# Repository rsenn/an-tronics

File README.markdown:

40106-4069-Synth \n\n 
555-Oscillator \n\n 
5V-to-12V-Converter \n\n 
Amazing-All-Band-Receiver \n\n 
Amplifier-ClassAB \n\n 
Aurel-super-regen-receiver-ASR2 \n\n 
FM-Radio-Circuit \n\n 
FM-Radio-Simple-Receiver \n\n 
FM-Simple-Regen \n\n 
Headphone-Amplifier-ClassAB-13x7 \n\n 
Headphone-Amplifier-ClassAB-alt3 \n\n 
Headphone-Amplifier-ClassAB-alt4 \n\n 
Headphone-Amplifier-ClassAB-alt \n\n 
Headphone-Amplifier-ClassAB \n\n 
MotorControllerOpto-BA6229 \n\n 
Simple-Analog-Amp-BC547 \n\n 
Simple-Charger-LiIon-OpampBased-LM324-prev \n\n 
Super-Regenerative-FM.old \n\n 
Super-Regenerative-VHF-2Transistor-RickAndersen-October2006-alt \n\n 
Super-Regenerative-VHF-KosmosX3000 \n\n 
Triangulator-LM324 \n\n 
VCF-LM324-Stereo+LFO-CableConn \n\n 
Simple-NPN-Regen-Receiver \n\n

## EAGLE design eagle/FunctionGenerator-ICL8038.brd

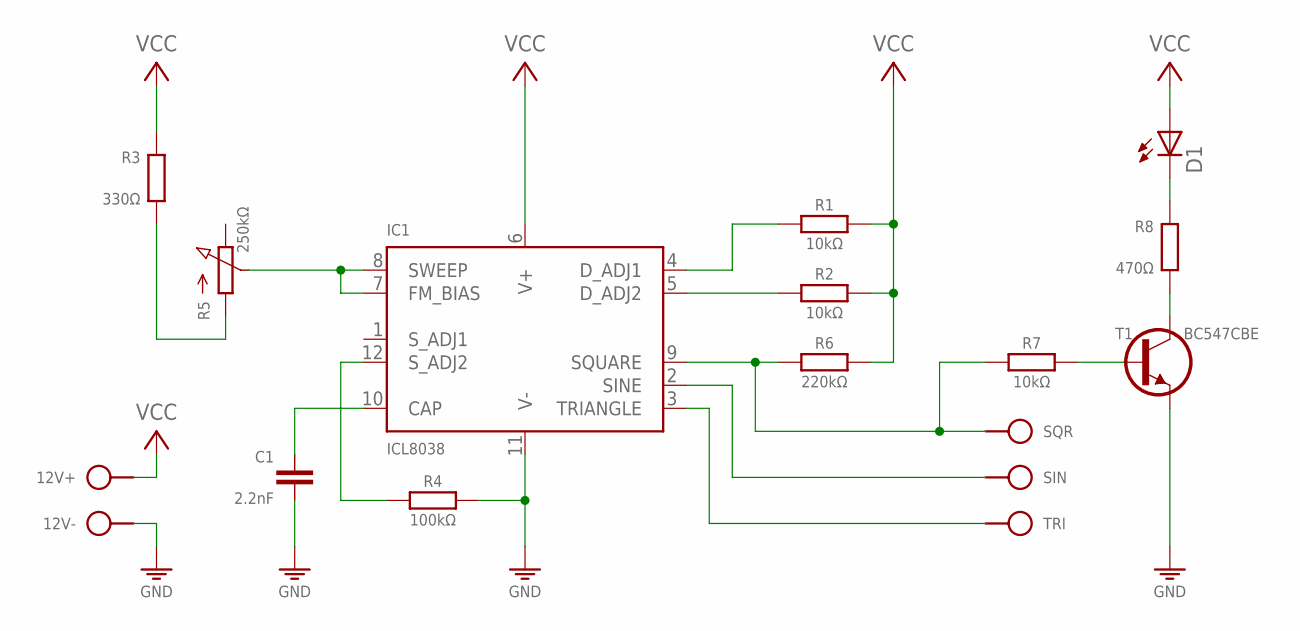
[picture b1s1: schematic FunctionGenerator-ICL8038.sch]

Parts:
12V: SPAD+-; SPAD-2
C1: 2.2nF; C050-020X044
D1: LED3MM
IC1: ICL8038; DIL14
R1, R2: 10kΩ; 0202/5
R3: 330Ω; 0202/5-V
R4: 100kΩ; 0202/5
R5: 250kΩ; POT
R6: 220kΩ; 0202/5-V
R7: 10kΩ; 0202/5-V
R8: 470Ω; 0202/5-V
SIN: SPAD
SQR: SPAD
T1: BC547CBE; TO92-CBE
TRI: SPAD

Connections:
GND: 12V.1, C1.2, IC1.11 (V-), R4.2, T1.E
unnamed: R3.1, R5.1 (A)
unnamed: IC1.4 (D_ADJ1), R1.1
unnamed: IC1.5 (D_ADJ2), R2.1
unnamed: IC1.9 (SQUARE), R6.1, R7.1, SQR.1
unnamed: IC1.12 (S_ADJ2), R4.1
unnamed: C1.1, IC1.10 (CAP)
unnamed: IC1.3 (TRIANGLE), TRI.1
unnamed: IC1.2 (SINE), SIN.1
unnamed: R7.2, T1.B
unnamed: D1.K (C), R8.2
unnamed: R8.1, T1.C
unnamed: IC1.7 (FM_BIAS), IC1.8 (SWEEP), R5.2 (S)
VCC: 12V.2, D1.A, IC1.6 (V+), R1.2, R2.2, R3.2, R6.2

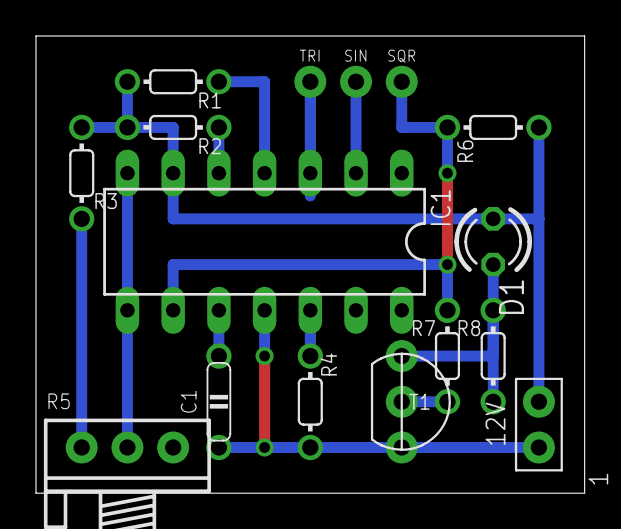
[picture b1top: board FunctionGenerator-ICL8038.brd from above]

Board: 2 copper layers, 30.5 x 25.4 mm, 16 parts (0 on the bottom side), 14 nets.

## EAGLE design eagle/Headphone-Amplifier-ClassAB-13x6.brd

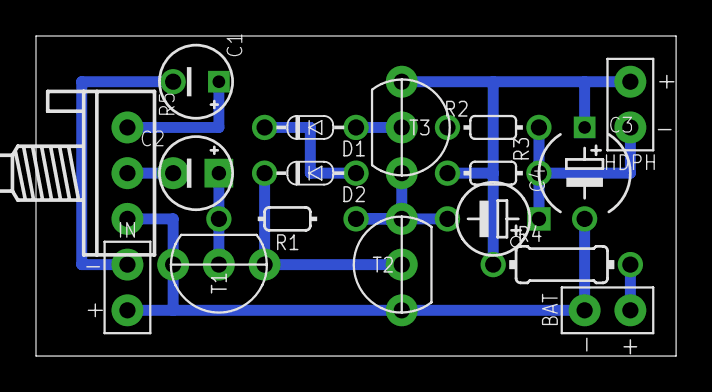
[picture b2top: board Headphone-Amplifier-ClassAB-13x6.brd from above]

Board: 2 copper layers, 35.6 x 17.8 mm, 17 parts (0 on the bottom side), 12 nets.

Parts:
BAT: SPAD+-+-; SPAD+-
C1: 4.7μF; E2.5-4/V
C2: 4.7μF; E2,5-4
C3: 100-1000μF; E5-5/V
C4: 220μF; E5-4
D1, D2: 1N4148; DO34-5
HDPH: SPAD+-+-; SPAD+-
IN: SPAD+-+-; SPAD+-
R1: 100kΩ; 0202/7
R2: 330Ω; 0202/5
R3: 100Ω; 0202/5-V
R4: 22Ω; 0204/7
R5: 100kΩ; POT
T1, T3: BC547; TO92-CBE
T2: BC557; TO92-CBE

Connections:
GND: BAT.1, C3.-, IN.2, R5.3, T1.E, T2.C
unnamed: D1.A, R2.1, T3.B
unnamed: D2.C, T1.C, T2.B
unnamed: D1.C, D2.A
unnamed: C4.-, R1.2, T2.E, T3.E
unnamed: C1.+, R5.1
unnamed: C2.-, R5.2
unnamed: C2.+, R1.1, T1.B
unnamed: C3.+, HDPH.2, R3.2, R4.1, T3.C
unnamed: C4.+, HDPH.1, R2.2, R3.1
unnamed: C1.-, IN.1
V+: BAT.2, R4.2

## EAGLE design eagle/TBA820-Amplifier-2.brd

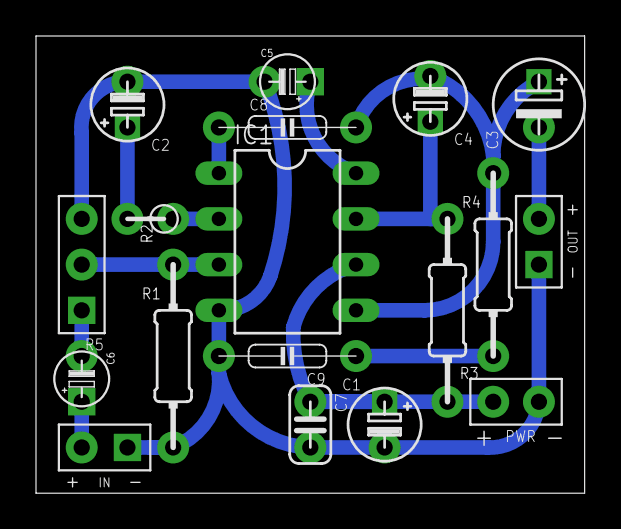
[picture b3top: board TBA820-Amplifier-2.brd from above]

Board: 2 copper layers, 30.5 x 25.4 mm, 18 parts (0 on the bottom side), 13 nets.

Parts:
C1, C2, C4: 100μF; E2.5-4/V
C3: 220μF; E2,5-5
C5: 47μF; E2,5-3
C6: 10μF; E2,5-3
C7: 100nF; C025-024X044
C8: 220pF; C075-020X044
C9: 220nF; C075-020X044
IC1: TBA820; DIL08
IN: SPAD+--+; SPAD-+
OUT: SPAD+-+-; SPAD+-
R1: 10kΩ; 0204/10-V
R2: 120Ω; 0202/2V
R3: 56Ω; 0204/10-V
R4: 1Ω; 0204/10-V
R5: 22kΩ; CONN-3P
S4: VCC_GNDPWR-L; PWR-L

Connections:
BOOT: C4.+, IC1.7, R3.2
FREQ: C8.1, IC1.1
GAIN: IC1.2, R2.1
GND: C1.-, C2.-, C5.-, C7.2, C9.2, IC1.4, IN.1, OUT.1, R1.2, R5.3, S4.1
INPUT: IC1.3, R1.1, R5.2
unnamed: C9.1, R4.2
unnamed: C6.-, R5.1
unnamed: C6.+, IN.2
unnamed: C3.-, OUT.2
unnamed: C2.+, R2.2
OUT: C3.+, C4.-, C8.2, IC1.5, R4.1
RIPPLE: C5.+, IC1.8
VCC: C1.+, C7.1, IC1.6, R3.1, S4.2

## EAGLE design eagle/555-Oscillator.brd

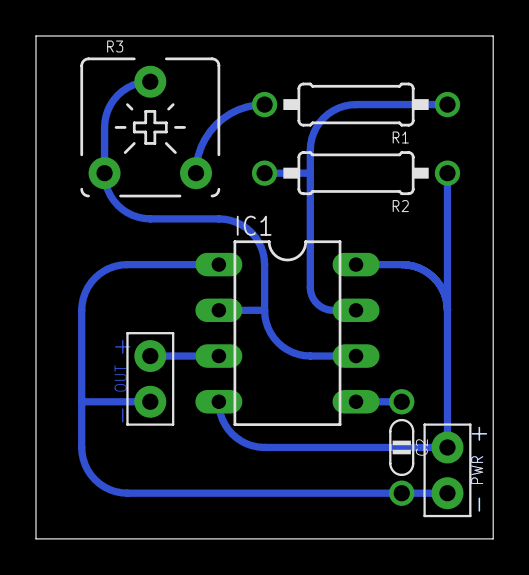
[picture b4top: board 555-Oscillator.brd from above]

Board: 2 copper layers, 25.4 x 27.9 mm, 7 parts (0 on the bottom side), 7 nets.

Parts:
C2: 10n; C050-020X036/V
IC1: 555; DIL08
OUT: SPAD+--+; SPAD-+
R1: 1kΩ; 0207/10
R2: 10kΩ; 0207/10
R3: 220kΩ; POT-V
S1: VCC_GNDPWR-R; PWR-R

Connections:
GND: C2.2, IC1.1, OUT.1, S1.1
unnamed: IC1.7, R1.1, R2.2
unnamed: R1.2, R3.E
unnamed: IC1.2, IC1.6, R3.A, R3.S
unnamed: C2.1, IC1.5
unnamed: IC1.3, OUT.2
VCC: IC1.4, IC1.8, R2.1, S1.2

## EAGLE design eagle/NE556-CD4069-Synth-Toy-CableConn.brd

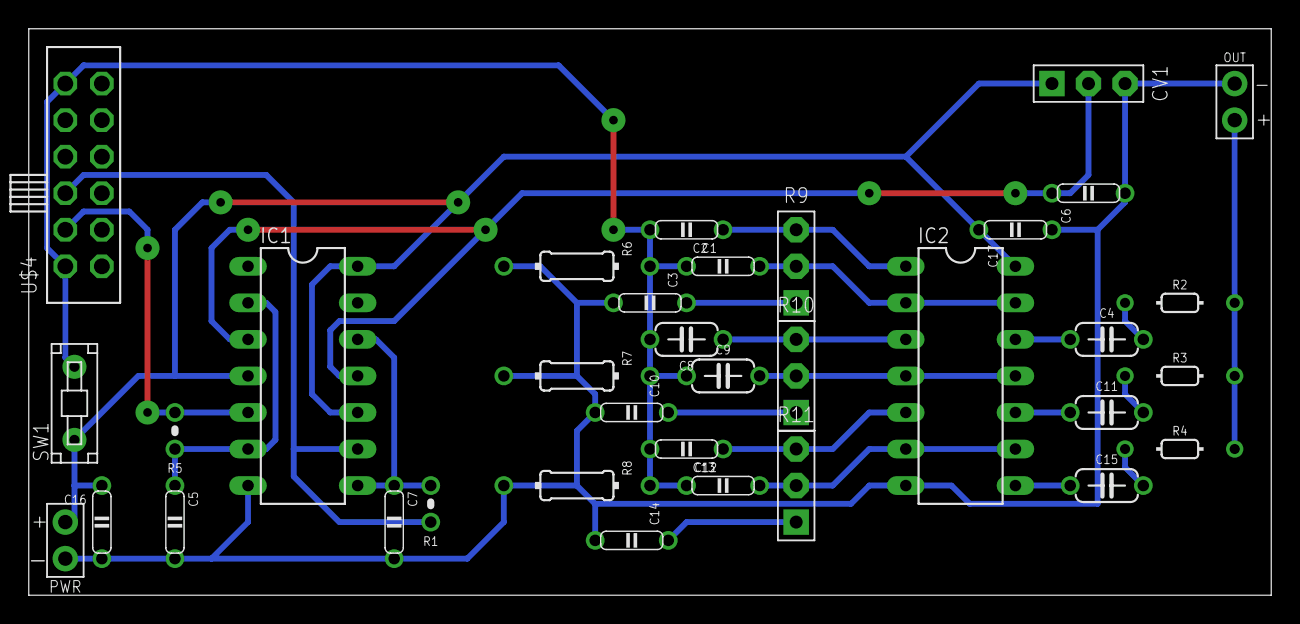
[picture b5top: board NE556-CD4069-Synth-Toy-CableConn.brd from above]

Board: 2 copper layers, 86.4 x 39.4 mm, 35 parts (0 on the bottom side), 24 nets.

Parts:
C1, C2, C5, C7: 100nF; C050-020X044
C3: 220nF; C050-020X044/V
C4, C11, C15: 470nF; C050-024X044
C6: 10nF; C050-020X044/V
C8, C9: 330nF; C050-024X044
C10, C14: 470nF; C050-020X044/V
C12, C13: 68nF; C050-020X044
C16, C17: 100nF; C050-020X044/V
CV1: 20kΩ; CONN-3P
IC1: LM556N; DIL14
IC2: 4069N; DIL14
OUT: SPAD-+
R1, R5: 33kΩ; 0204/2V
R2, R3, R4: R-H0202/7; 0202/7
R6, R7, R8: 10kΩ; 0204/10-V
R9, R10, R11: 100kΩ; CONN-3P
S3: VCC_GNDPWR-L; PWR-L
SW1: PB-1P-1T; PB-1P1T
U$4: SL-SW-2P-4T; SLSW-2P4T-2-H

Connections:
GND: C3.2, C5.2, C6.2, C7.2, C10.2, C14.2, C16.2, C17.2, CV1.3, IC1.7, IC2.7, OUT.1, R6.2, R7.2, R8.2, S3.1
unnamed: C2.2, IC2.2, IC2.13, R9.2
unnamed: IC1.5, R5.2, U$4.A2
unnamed: C4.2, R2.1
unnamed: C3.1, R9.1
unnamed: C14.1, R11.1
unnamed: C4.1, IC2.12
unnamed: C1.1, IC2.1, R9.3
unnamed: C5.1, IC1.2, IC1.6, R5.1
unnamed: C6.1, CV1.2, IC1.3, IC1.11
unnamed: C12.1, IC2.5, R11.3
unnamed: IC1.9, R1.1, U$4.A3
unnamed: C7.1, IC1.8, IC1.12, R1.2
unnamed: C8.1, IC2.3, R10.3
unnamed: C13.2, IC2.6, IC2.9, R11.2
unnamed: C15.1, IC2.8
unnamed: C11.2, R3.1
unnamed: C11.1, IC2.10
unnamed: OUT.2, R2.2, R3.2, R4.2
unnamed: C9.2, IC2.4, IC2.11, R10.2
unnamed: C15.2, R4.1
unnamed: C10.1, R10.1
TRIG1: C1.2, C2.1, C8.2, C9.1, C12.2, C13.1, R6.1, R7.1, R8.1, SW1.1, U$4.A1, U$4.A6
VCC: C16.1, C17.1, CV1.1, IC1.4, IC1.10, IC1.14, IC2.14, S3.2, SW1.2

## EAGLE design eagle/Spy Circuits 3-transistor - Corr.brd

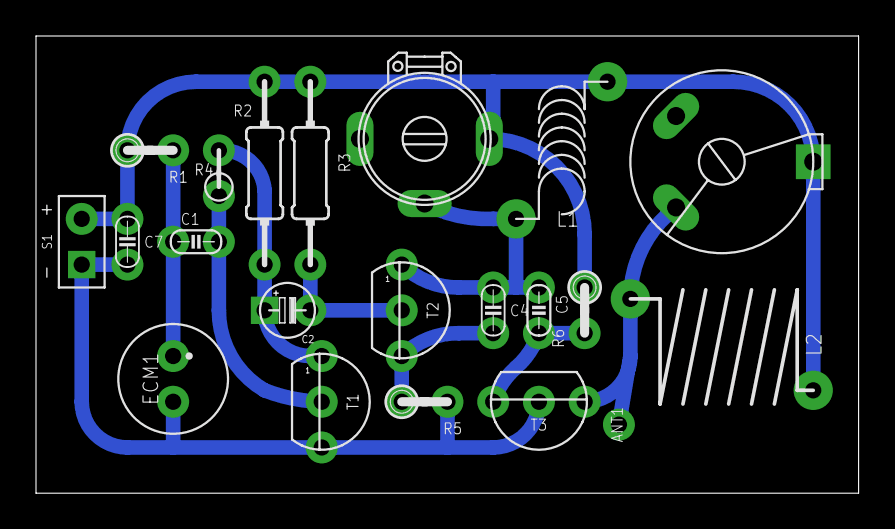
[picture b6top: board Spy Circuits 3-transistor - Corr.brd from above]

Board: 2 copper layers, 45.7 x 25.4 mm, 21 parts (0 on the bottom side), 10 nets.

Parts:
ANT1: ANT; SPAD
C1: 22nF; C025-015X024
C2: 1µF; E2,5-3
C3: 2 - 10pF; TRIM-2222-808-45
C4: 10pF; C025-015X024/V
C5: 10pF; C025-015X024
C6: 5 - 30pF; TRIM-C-BIG
C7: C025-015X024/V
ECM1: ECM-4
L1: 0.1µH; L-04/8V-2-M
L2: 0.2µH; L-08-10/5
R1: 22kΩ; 0204/2
R2: 22kΩ; 0204/10-V
R3: 47kΩ; 0204/10
R4: 1MΩ; 0202/2V
R5: 470Ω; 0204/2
R6: 150kΩ; 0204/2
S1: VCC_GNDL; SPAD-+
T1, T2: BC547; TO92
T3: BF959; TO92-CEB

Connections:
GND: C7.2, ECM1.2, R5.2, S1.1, T1.3, T3.E
unnamed: C2.+, R2.2, R4.2, T1.1
unnamed: C1.2, R4.1, T1.2
unnamed: C1.1, ECM1.1, R1.2
unnamed: C4.2, R5.1, T2.3
unnamed: C2.-, R3.2, T2.2
unnamed: C3.2, C4.1, C5.1, L1.1, T2.1
unnamed: C5.2, R6.2, T3.B
unnamed: ANT1.1, C6.P$1, L2.2, T3.C
VCC: C3.1, C6.P$3, C7.1, L1.2, L2.1, R1.1, R2.1, R3.1, R6.1, S1.2

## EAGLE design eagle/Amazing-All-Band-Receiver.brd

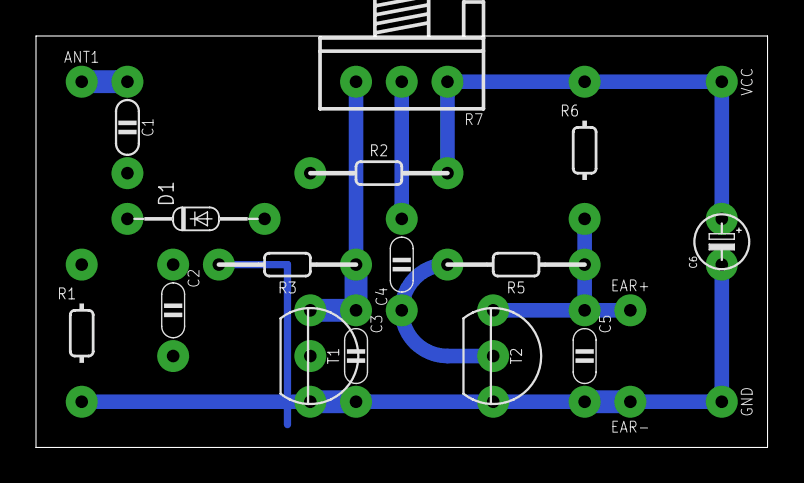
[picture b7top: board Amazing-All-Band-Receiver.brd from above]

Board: 2 copper layers, 40.6 x 22.9 mm, 20 parts (0 on the bottom side), 10 nets.

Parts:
ANT1: ANT; SPAD
C1: 100p; C050-020X036/V
C2, C4: 10n; C050-020X036
C3, C5: 1n; C050-020X036
C6: 1u; E2,5-3
D1: 1N34; DO34-7V
EAR+: SPAD
EAR-: SPAD
GND: SPAD
R1: 10kΩ; 0202/7-V
R2, R3, R5: 10MΩ; 0202/7
R6: 100kΩ; 0202/7-V
R7: 100kΩ; POT
T1, T2: BC547; TO92-CBE
VCC: SPAD

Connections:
AC: C1.2, D1.C, R1.1
ANT: ANT1.1, C1.1
DC: C2.2, D1.A, R2.1
GND: C3.2, C5.2, C6.-, EAR-.1, GND.1, R1.2, T1.3, T2.3
I1: C2.1, R3.2, T1.2
I2: C4.1, R5.2, T2.2
O1: C3.1, R3.1, R7.E, T1.1
O2: C5.1, EAR+.1, R5.1, R6.2, T2.1
VCC: C6.+, R2.2, R6.1, R7.A, VCC.1
VO1: C4.2, R7.S

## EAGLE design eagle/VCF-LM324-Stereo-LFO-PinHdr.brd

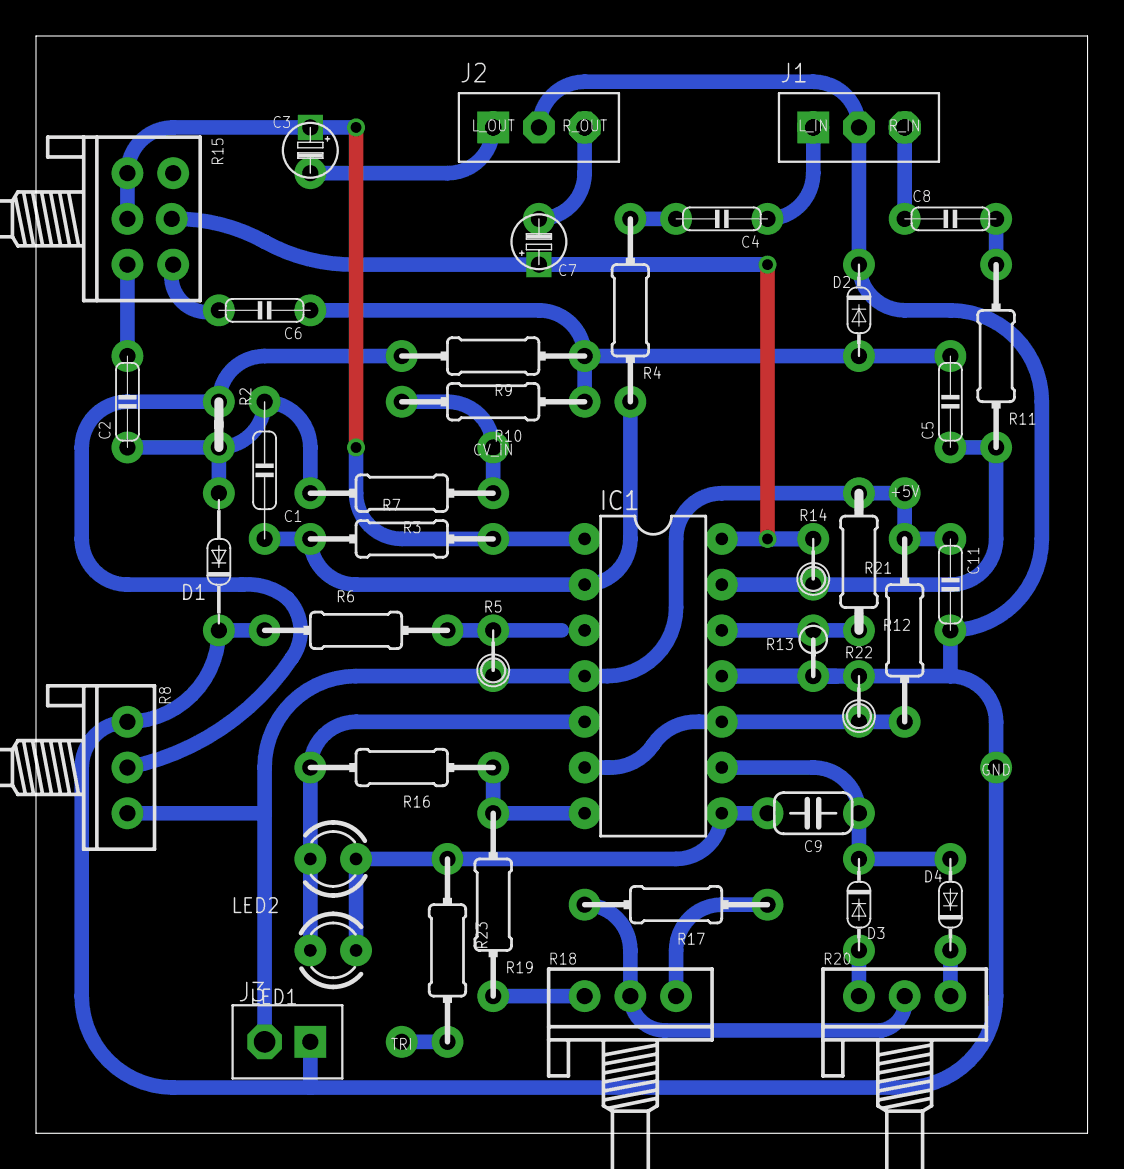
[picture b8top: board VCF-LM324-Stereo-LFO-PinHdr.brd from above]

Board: 2 copper layers, 58.4 x 61.0 mm, 50 parts (0 on the bottom side), 31 nets.

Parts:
+5V: VCC; SPAD
C1: 0.1μF; C075-020X044/V
C2: 0.1μF; C050-020X044
C3, C7: 1μF; E2,5-3/V
C4, C8: 1μF; C050-020X044
C5, C6, C11: 100nF; C050-020X044
C9: 1μF; C050-024X044
CV_IN: CV_IN; SPAD
D1: 1N4148; DO34-7V
D2: 1N4148; DO34-5-V
D3, D4: 1N4148; DO34-5V
GND: GND; SPAD
IC1: LM324; DIL14
J1: A_IN; CONN-3P
J2: A_OUT; CONN-3P
J3: CONN-2P2P/H; CONN-2P
LED1, LED2: LED3MM
L_IN: AUDIO_IN; SPAD
L_OUT: AUDIO_OUT; SPAD
R2: 1kΩ; 0204V
R3, R9, R10, R23: 1kΩ; 0204/10
R4, R11: 470kΩ; 0204/10-V
R5, R14, R22: 100kΩ; 0204/2V
R6, R7: 100kΩ; 0204/10
R8: POT
R12: 100kΩ; 0204/7-V
R13: 100kΩ; 0202V
R15: 10kΩ; POT-STEREO-2X3
R16: 47kΩ; 0204/10
R17: 4.7kΩ; 0204/10
R18: 10kΩ; POT
R19: 4.7kΩ; 0204/10-V
R20: 100kΩ; POT
R21: 100kΩ; 0204/10-V
R_IN: AUDIO_IN; SPAD
R_OUT: AUDIO_OUT; SPAD
TRI: TRIANGLE; SPAD

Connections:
GND: C11.2, D1.C, D2.C, GND.1, IC1.11, J1.2, J2.2, J3.1, R6.1, R8.A, R13.1, R22.1
LEFT_IN: C4.1, J1.1, L_IN.1
LEFT_OUT: C3.-, J2.1, L_OUT.1
unnamed: C6.2, R15.2-E
unnamed: C1.1, IC1.2, R4.1, R7.1
unnamed: C2.2, R15.1-E
unnamed: C3.+, IC1.1, R7.2, R15.1-S
unnamed: R2.1, R8.S, R9.2
unnamed: IC1.3, R5.1, R6.2
unnamed: CV_IN.1, R3.1, R10.2
unnamed: C1.2, C2.1, D1.A, R2.2, R3.2
unnamed: C4.2, R4.2
unnamed: C7.+, IC1.14, R14.1, R15.2-S
unnamed: IC1.12, R12.1, R13.2
unnamed: IC1.7, R16.1, R19.2
unnamed: IC1.5, LED1.A, LED2.K, R16.2
unnamed: C5.2, C6.1, D2.A, R9.1, R10.1
unnamed: C5.1, IC1.13, R11.1, R14.2
unnamed: C8.2, R11.2
unnamed: C9.1, D3.C, D4.A, IC1.9
unnamed: C9.2, IC1.8, LED1.K, LED2.A, R23.1
OA_C_IN+: IC1.6, IC1.10, R21.2, R22.2
RIGHT_IN: C8.1, J1.3, R_IN.1
RIGHT_OUT: C7.-, J2.3, R_OUT.1
TRIM_1_A: D3.A, R20.A
TRIM_1_B: D4.C, R20.E
TRIM_2_A: R17.1, R18.E
TRIM_2_B: R18.A, R19.1
TRIM_P: R17.2, R18.S, R20.S
TRI_OUT: R23.2, TRI.1
VCC: +5V.1, C11.1, IC1.4, J3.2, R5.2, R8.E, R12.2, R21.1

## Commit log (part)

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2020-04-30 updated libraries
2021-05-27 removed polygons
